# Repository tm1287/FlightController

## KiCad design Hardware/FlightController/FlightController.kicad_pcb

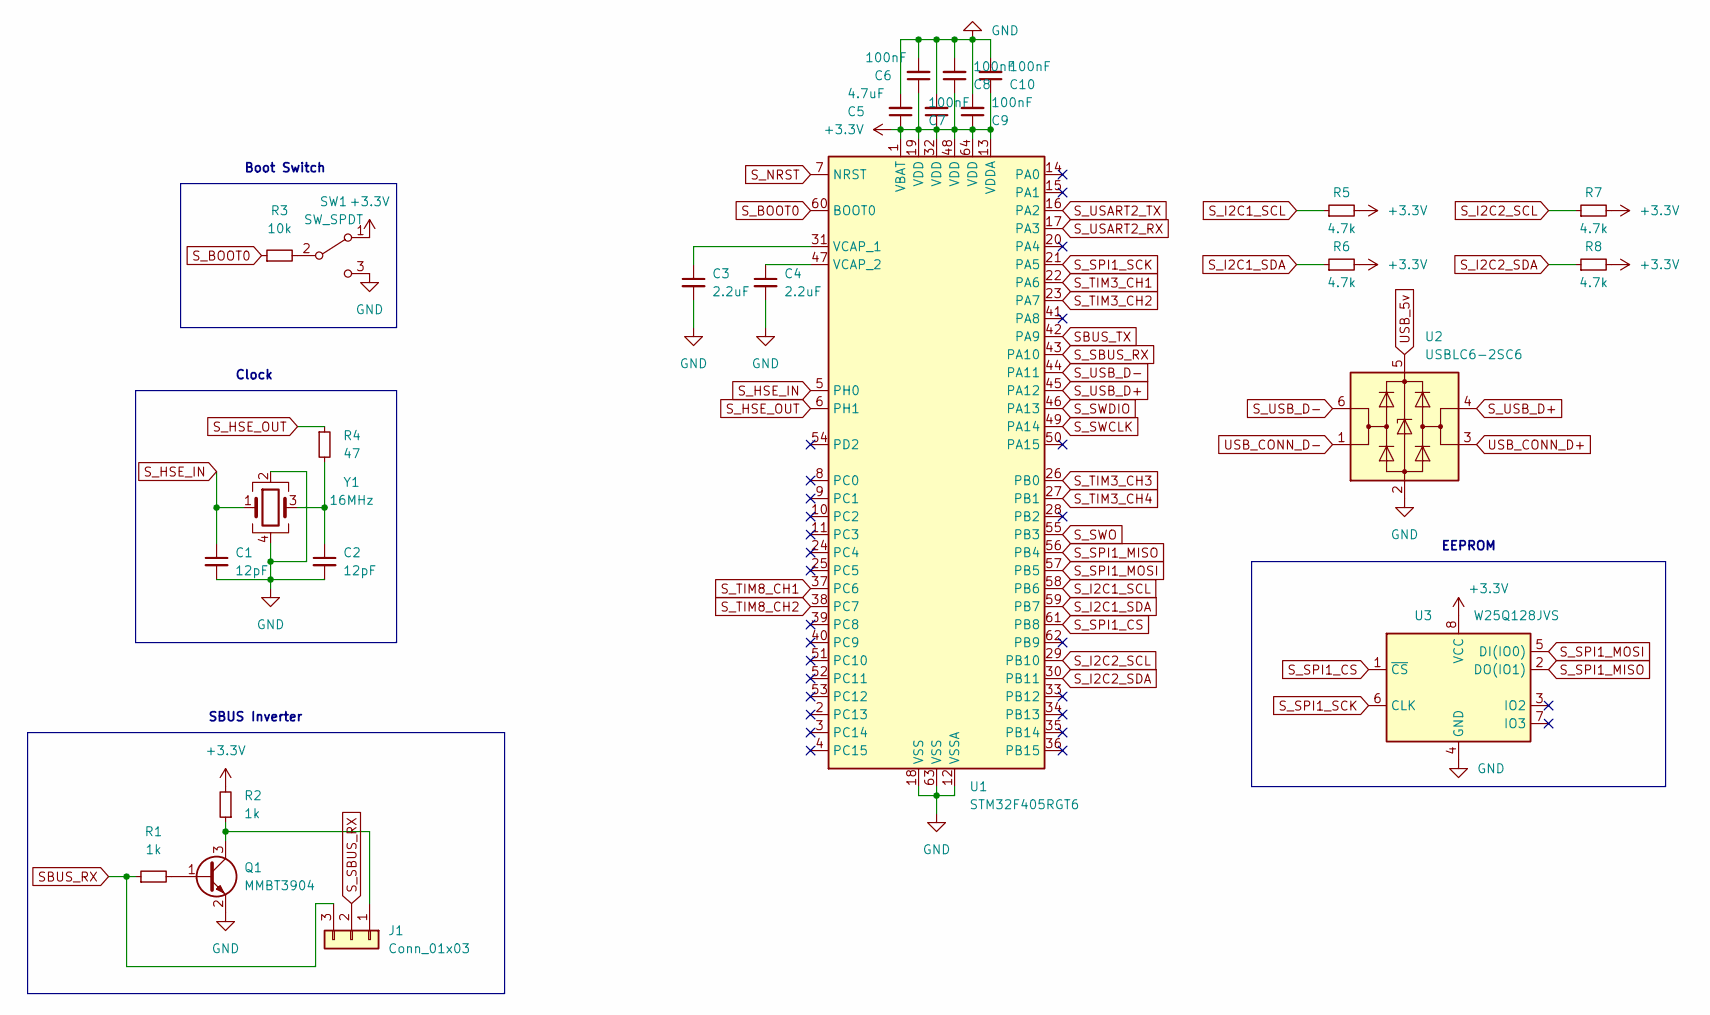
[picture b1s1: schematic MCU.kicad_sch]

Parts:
C1, C2: 12pF; C_0402_1005Metric; LCSC C1547
C3, C4: 2.2uF; C_0402_1005Metric; LCSC C12530
C5: 4.7uF; C_0603_1608Metric; LCSC C19666
C6, C7, C8, C9, C10: 100nF; C_0402_1005Metric; LCSC C1525
J1: Conn_01x03; PinHeader_1x03_P2.54mm_Vertical
Q1: MMBT3904; SOT-23; LCSC C20526
R1, R2: 1k; R_0603_1608Metric; LCSC C21190
R3: 10k; R_0603_1608Metric; LCSC C25804
R4: 47; R_0402_1005Metric; LCSC C25118
R5, R6, R7, R8: 4.7k; R_0402_1005Metric; LCSC C25900
SW1: SW_SPDT; Switch_Slide_11.6x4mm_EG1218
U1: STM32F405RGT6; LQFP-64_10x10mm_P0.5mm; LCSC C15742
U2: USBLC6-2SC6; SOT-23-6; LCSC C2827654
U3: W25Q128JVS; SOIC-8_5.23x5.23mm_P1.27mm; LCSC C97521
Y1: 16MHz; Crystal_SMD_3225-4Pin_3.2x2.5mm; LCSC C13738

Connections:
+3V3: C5.1, C6.1, C7.1, C8.1, C9.1, C10.1, R2.2, R5.2, R6.2, R7.2, R8.2, SW1.1 (A), U1.1 (VBAT), U1.13 (VDDA), U1.19 (VDD), U1.32 (VDD), U1.48 (VDD), U1.64 (VDD), U3.8 (VCC); also elsewhere on the board
GND: C1.2, C2.2, C3.2, C4.2, C5.2, C6.2, C7.2, C8.2, C9.2, C10.2, Q1.2 (E), SW1.3 (C), U1.12 (VSSA), U1.18 (VSS), U1.63 (VSS), U2.2 (GND), U3.4 (GND), Y1.2, Y1.4; also elsewhere on the board
unnamed: C2.1, R4.2, Y1.3
unnamed: C3.1, U1.31 (VCAP_1)
unnamed: C4.1, U1.47 (VCAP_2)
unnamed: J1.1, Q1.3 (C), R2.1
unnamed: Q1.1 (B), R1.2
unnamed: R3.2, SW1.2 (B)
SBUS_RX: J1.3, R1.1; also elsewhere on the board
SBUS_TX: U1.42 (PA9); also elsewhere on the board
S_BOOT0: R3.1, U1.60 (BOOT0)
S_HSE_IN: C1.1, U1.5 (PH0), Y1.1
S_HSE_OUT: R4.1, U1.6 (PH1)
S_I2C1_SCL: R5.1, U1.58 (PB6); also elsewhere on the board
S_I2C1_SDA: R6.1, U1.59 (PB7); also elsewhere on the board
S_I2C2_SCL: R7.1, U1.29 (PB10); also elsewhere on the board
S_I2C2_SDA: R8.1, U1.30 (PB11); also elsewhere on the board
S_NRST: U1.7 (NRST); also elsewhere on the board
S_SBUS_RX: J1.2, U1.43 (PA10)
S_SPI1_CS: U1.61 (PB8), U3.1 (~CS)
S_SPI1_MISO: U1.56 (PB4), U3.2 (DO(IO1))
S_SPI1_MOSI: U1.57 (PB5), U3.5 (DI(IO0))
S_SPI1_SCK: U1.21 (PA5), U3.6 (CLK)
S_SWCLK: U1.49 (PA14); also elsewhere on the board
S_SWDIO: U1.46 (PA13); also elsewhere on the board
S_SWO: U1.55 (PB3); also elsewhere on the board
S_TIM3_CH1: U1.22 (PA6); also elsewhere on the board
S_TIM3_CH2: U1.23 (PA7); also elsewhere on the board
S_TIM3_CH3: U1.26 (PB0); also elsewhere on the board
S_TIM3_CH4: U1.27 (PB1); also elsewhere on the board
S_TIM8_CH1: U1.37 (PC6); also elsewhere on the board
S_TIM8_CH2: U1.38 (PC7); also elsewhere on the board
S_USART2_RX: U1.17 (PA3); also elsewhere on the board
S_USART2_TX: U1.16 (PA2); also elsewhere on the board
S_USB_D+: U1.45 (PA12), U2.4 (I/O2)
S_USB_D-: U1.44 (PA11), U2.6 (I/O1)
USB_5v: U2.5 (VBUS); also elsewhere on the board
USB_CONN_D+: U2.3 (I/O2); also elsewhere on the board
USB_CONN_D-: U2.1 (I/O1); also elsewhere on the board

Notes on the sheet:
Clock
Boot Switch
SBUS Inverter
EEPROM

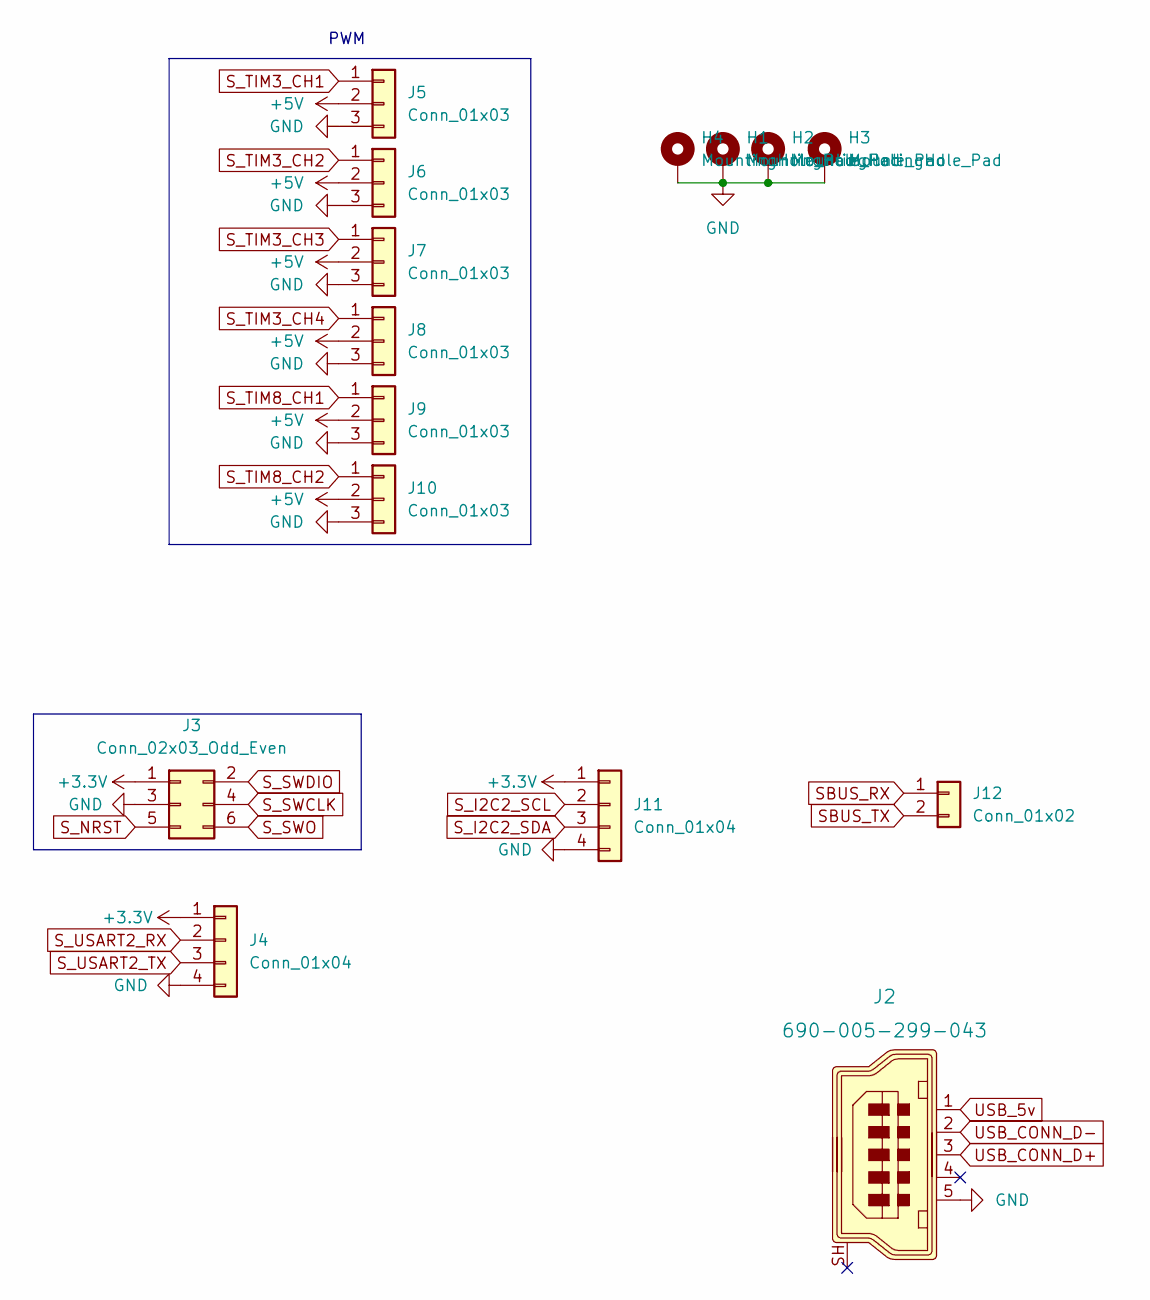
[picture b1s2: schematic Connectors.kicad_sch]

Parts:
H1, H2, H3, H4: MountingHole_Pad; MountingHole_2.5mm_Pad
J2: 690-005-299-043; USB_Mini_B_Female_690-005-299-043; MPN 690-005-299-043; Digi-Key_PN 151-1206-1-ND
J3: Conn_02x03_Odd_Even; PinHeader_2x03_P2.54mm_Vertical
J4, J11: Conn_01x04; PinHeader_1x04_P2.54mm_Vertical
J5, J6, J7, J8, J9, J10: Conn_01x03; PinHeader_1x03_P2.54mm_Vertical
J12: Conn_01x02; PinHeader_1x02_P2.54mm_Vertical

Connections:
+3V3: J3.1, J4.1, J11.1; also elsewhere on the board
+5V: J5.2, J6.2, J7.2, J8.2, J9.2, J10.2; also elsewhere on the board
GND: H1.1, H2.1, H3.1, H4.1, J2.5, J3.3, J4.4, J5.3, J6.3, J7.3, J8.3, J9.3, J10.3, J11.4; also elsewhere on the board
SBUS_RX: J12.1; also elsewhere on the board
SBUS_TX: J12.2; also elsewhere on the board
S_I2C2_SCL: J11.2; also elsewhere on the board
S_I2C2_SDA: J11.3; also elsewhere on the board
S_NRST: J3.5; also elsewhere on the board
S_SWCLK: J3.4; also elsewhere on the board
S_SWDIO: J3.2; also elsewhere on the board
S_SWO: J3.6; also elsewhere on the board
S_TIM3_CH1: J5.1; also elsewhere on the board
S_TIM3_CH2: J6.1; also elsewhere on the board
S_TIM3_CH3: J7.1; also elsewhere on the board
S_TIM3_CH4: J8.1; also elsewhere on the board
S_TIM8_CH1: J9.1; also elsewhere on the board
S_TIM8_CH2: J10.1; also elsewhere on the board
S_USART2_RX: J4.2; also elsewhere on the board
S_USART2_TX: J4.3; also elsewhere on the board

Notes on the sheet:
PWM

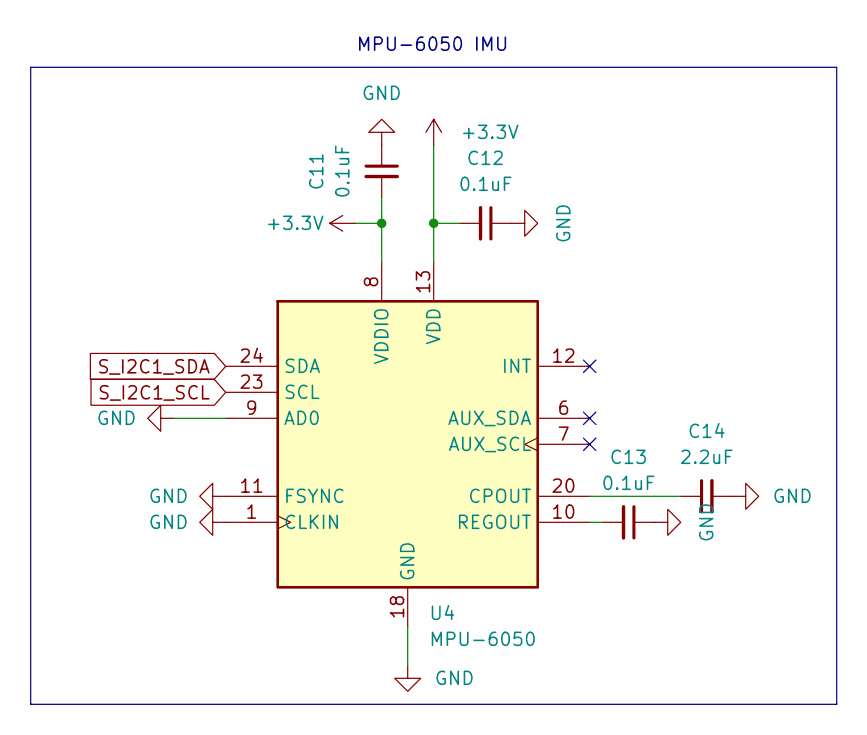
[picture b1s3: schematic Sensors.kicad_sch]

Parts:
C11, C12, C13: 0.1uF; C_0603_1608Metric_Pad1.08x0.95mm_HandSolder
C14: 2.2uF; C_0402_1005Metric; LCSC C12530
U4: MPU-6050; InvenSense_QFN-24_4x4mm_P0.5mm; LCSC C24112

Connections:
+3V3: C11.2, C12.2, U4.8 (VDDIO), U4.13 (VDD); also elsewhere on the board
GND: C11.1, C12.1, C13.1, C14.2, U4.1 (CLKIN), U4.9 (AD0), U4.11 (FSYNC), U4.18 (GND); also elsewhere on the board
unnamed: C13.2, U4.10 (REGOUT)
unnamed: C14.1, U4.20 (CPOUT)
S_I2C1_SCL: U4.23 (SCL); also elsewhere on the board
S_I2C1_SDA: U4.24 (SDA); also elsewhere on the board

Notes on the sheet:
MPU-6050 IMU

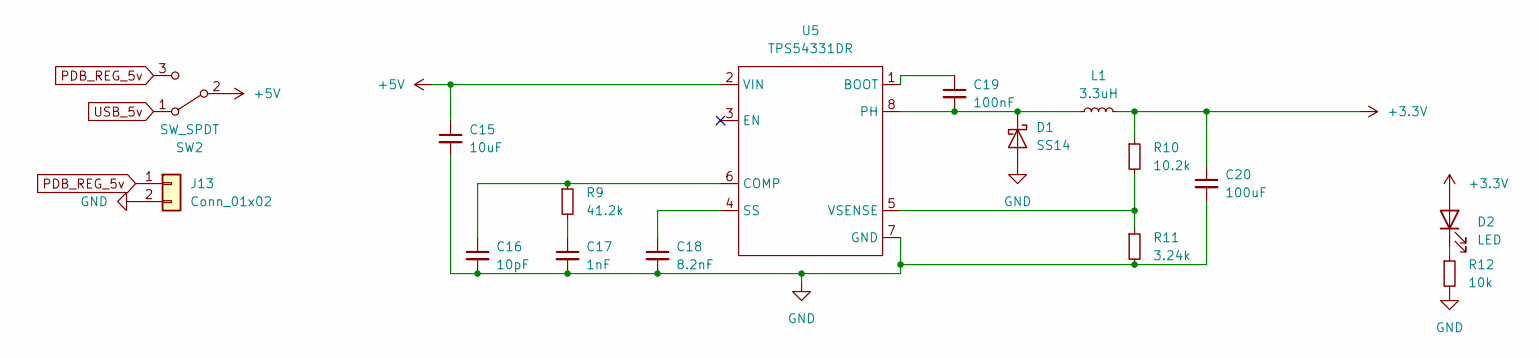
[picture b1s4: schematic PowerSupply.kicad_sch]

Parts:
C15: 10uF; C_0603_1608Metric; LCSC C96446
C16: 10pF; C_0603_1608Metric; LCSC C1634
C17: 1nF; C_0603_1608Metric; LCSC C1588
C18: 8.2nF; C_0603_1608Metric; LCSC C27920
C19: 100nF; C_0603_1608Metric; LCSC C14663
C20: 100uF; C_1206_3216Metric; LCSC C15008
D1: SS14; D_SMA; LCSC C2480
D2: LED; LED_0603_1608Metric; LCSC C2286
J13: Conn_01x02; PinHeader_1x02_P2.54mm_Vertical
L1: 3.3uH; L_1008_2520Metric_Pad1.43x2.20mm_HandSolder
R9: 41.2k; R_0603_1608Metric_Pad0.98x0.95mm_HandSolder
R10: 10.2k; R_0805_2012Metric_Pad1.20x1.40mm_HandSolder
R11: 3.24k; R_0603_1608Metric_Pad0.98x0.95mm_HandSolder
R12: 10k; R_0603_1608Metric; LCSC C25804
SW2: SW_SPDT; Switch_Slide_11.6x4mm_EG1218
U5: TPS54331DR; SOIC-8_3.9x4.9mm_P1.27mm; LCSC C9865

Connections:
+3V3: C20.1, D2.2 (A), L1.2, R10.1; also elsewhere on the board
+5V: C15.1, SW2.2 (B), U5.2 (VIN); also elsewhere on the board
GND: C15.2, C16.2, C17.2, C18.2, C20.2, D1.2 (A), J13.2, R11.2, R12.2, U5.7 (GND); also elsewhere on the board
unnamed: C16.1, R9.1, U5.6 (COMP)
unnamed: C17.1, R9.2
unnamed: C18.1, U5.4 (SS)
unnamed: C19.1, U5.1 (BOOT)
unnamed: C19.2, D1.1 (K), L1.1, U5.8 (PH)
unnamed: D2.1 (K), R12.1
unnamed: R10.2, R11.1, U5.5 (VSENSE)
PDB_REG_5v: J13.1, SW2.3 (C)
USB_5v: SW2.1 (A); also elsewhere on the board

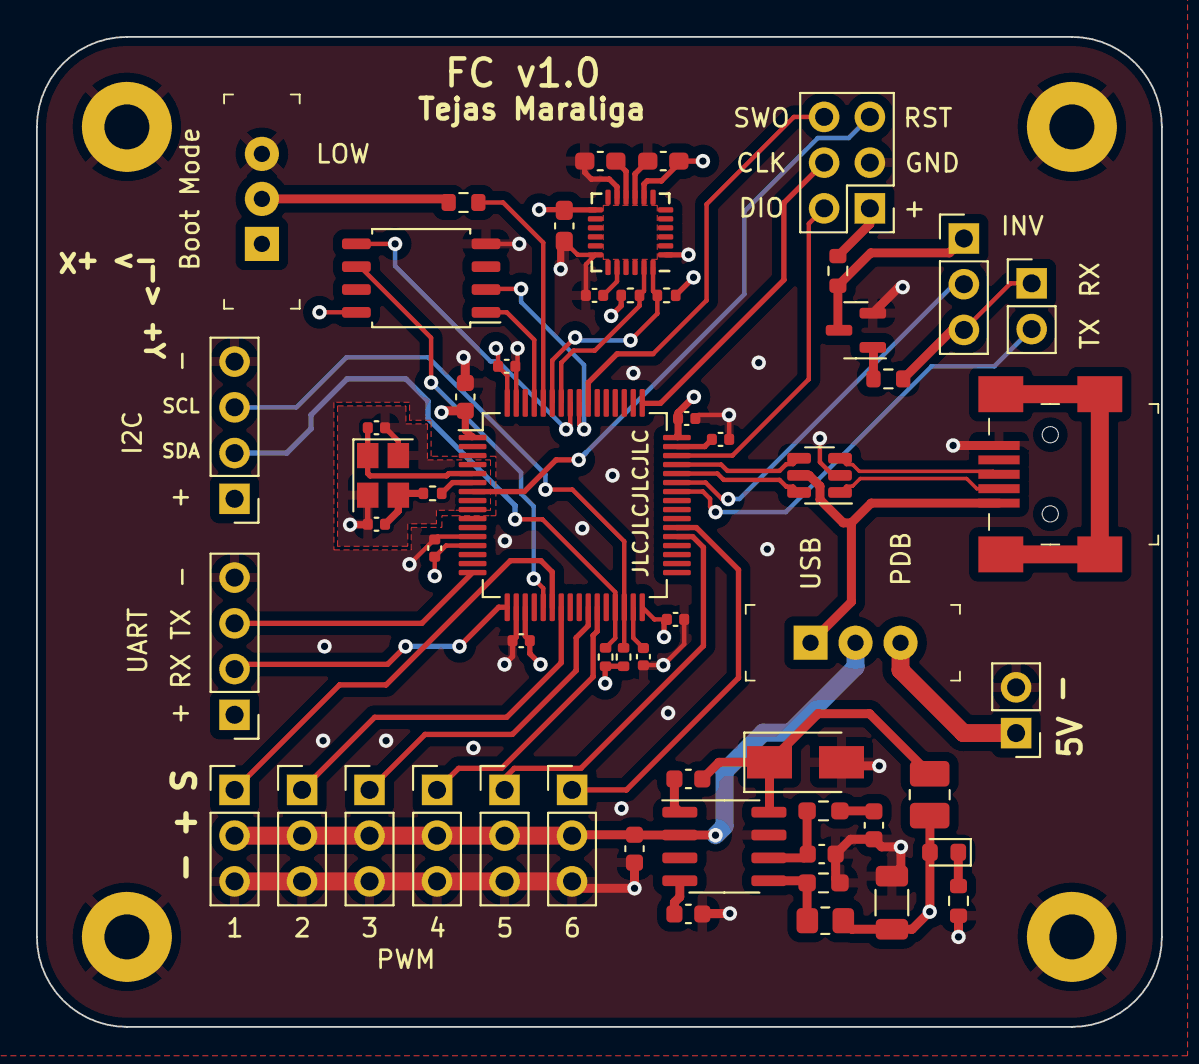
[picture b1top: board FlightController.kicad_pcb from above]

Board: 4 copper layers, 62.5 x 55.0 mm, 61 parts (0 on the bottom side), 50 nets.

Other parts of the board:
Je: 690-005-299-043; USB_Mini_B_Female_690-005-299-043

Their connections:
GND: Je.5; also elsewhere on the board
USB_5v: Je.1; also elsewhere on the board
USB_CONN_D+: Je.3; also elsewhere on the board
USB_CONN_D-: Je.2; also elsewhere on the board

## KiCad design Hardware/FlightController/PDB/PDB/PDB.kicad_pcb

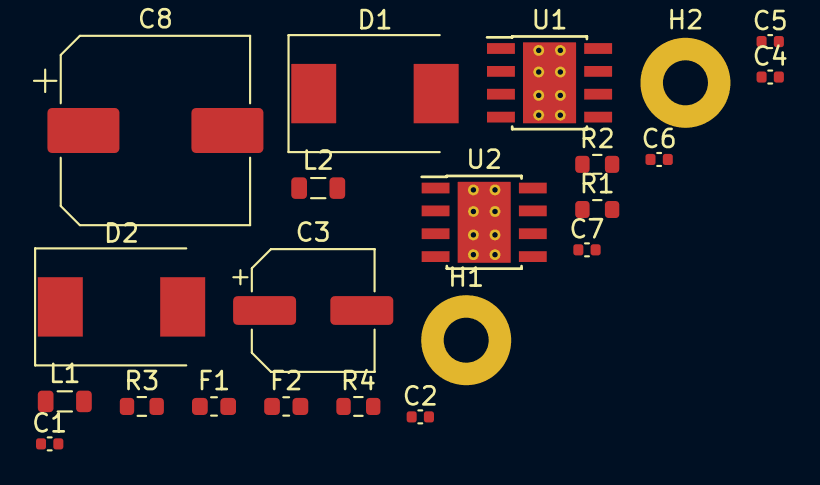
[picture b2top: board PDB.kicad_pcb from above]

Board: 2 copper layers, 22 parts (0 on the bottom side), 10 nets, no tracks yet.

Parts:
C1, C2, C4, C5, C6, C7: 10uF; C_0402_1005Metric
C3: 330uF; CP_Elec_6.3x5.8
C8: 220uF; CP_Elec_10x10
D1, D2: B340; D_SMC
F1, F2: 750mA; Fuse_0603_1608Metric
H1, H2: MountingHole_Pad; MountingHole_2.5mm_Pad
L1, L2: 22 uH; L_0805_2012Metric
R1, R3: 10k; R_0603_1608Metric
R2: 5.9k; R_0603_1608Metric
R4: 3.24k; R_0603_1608Metric
U1, U2: TPS5430DDA; TI_SO-PowerPAD-8_ThermalVias

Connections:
+BATT: C1.1, C4.1, C5.1, C6.1, H1.1, U1.7 (VIN), U2.7 (VIN)
GND: C1.2, C3.2, C4.2, C5.2, C6.2, C8.2, D1.2 (A), D2.2 (A), H2.1, R2.2, R4.2, U1.6 (GND), U1.9 (GNDPAD), U2.6 (GND), U2.9 (GNDPAD)
unnamed: C2.1, U1.1 (BOOT)
unnamed: C2.2, D1.1 (K), L1.1, U1.8 (PH)
unnamed: C3.1, F1.1, L1.2, R1.1
unnamed: C7.1, U2.1 (BOOT)
unnamed: C7.2, D2.1 (K), L2.1, U2.8 (PH)
unnamed: C8.1, F2.1, L2.2, R3.1
unnamed: R1.2, R2.1, U1.4 (VSENSE)
unnamed: R3.2, R4.1, U2.4 (VSENSE)

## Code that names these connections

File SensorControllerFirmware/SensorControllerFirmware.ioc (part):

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Mcu.Name=STM32F405RGTx
Mcu.Package=LQFP64
Mcu.UserName=STM32F405RGTx
PA10.Mode=Asynchronous
PA10.Signal=USART1_RX
PA11.Mode=Device_Only
PA11.Signal=USB_OTG_FS_DM
PA12.Mode=Device_Only
PA12.Signal=USB_OTG_FS_DP
PA13.Mode=Trace_Asynchronous_SW
PA13.Signal=SYS_JTMS-SWDIO
PA14.Mode=Trace_Asynchronous_SW
PA14.Signal=SYS_JTCK-SWCLK
PA2.Mode=Asynchronous
PA2.Signal=USART2_TX
PA3.Mode=Asynchronous
PA3.Signal=USART2_RX
PA5.Mode=Full_Duplex_Master
PA5.Signal=SPI1_SCK
PA6.Signal=S_TIM3_CH1
PA7.Signal=S_TIM3_CH2
PA9.Mode=Asynchronous
PA9.Signal=USART1_TX
PB0.Signal=S_TIM3_CH3
PB1.Signal=S_TIM3_CH4
PB10.Mode=I2C
PB10.Signal=I2C2_SCL
PB11.Mode=I2C
PB11.Signal=I2C2_SDA
PB3.Mode=Trace_Asynchronous_SW
PB3.Signal=SYS_JTDO-SWO
PB4.Mode=Full_Duplex_Master
PB4.Signal=SPI1_MISO
PB5.Mode=Full_Duplex_Master
PB5.Signal=SPI1_MOSI
PB6.Mode=I2C
PB6.Signal=I2C1_SCL
PB7.Mode=I2C
PB7.Signal=I2C1_SDA
PB8.GPIOParameters=PinState,GPIO_Label
PB8.GPIO_Label=EEPROM_CS
PB8.PinState=GPIO_PIN_SET
PB8.Signal=GPIO_Output
PC6.Signal=S_TIM8_CH1
PC7.Signal=S_TIM8_CH2
PH0-OSC_IN.Mode=HSE-External-Oscillator
PH0-OSC_IN.Signal=RCC_OSC_IN
PH1-OSC_OUT.Mode=HSE-External-Oscillator
PH1-OSC_OUT.Signal=RCC_OSC_OUT
RCC.HSE_VALUE=16000000
RCC.SYSCLKFreq_VALUE=168000000
RCC.SYSCLKSource=RCC_SYSCLKSOURCE_PLLCLK
board=custom

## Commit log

2022-05-31 Add Sensor MCU schematic items
2022-05-31 Rename firmware for transparency
2022-05-31 Add ICM-42670-P symbol and schematic
2022-06-09 Round out basic schematic and add preliminary board layout
2022-06-13 Add and route SBUS inverter
2022-06-15 Update footprints to be digikey compliant
2022-06-16 Update footprints, routing and LCSC numbers
2022-06-21 Finalize design and routing for v1.0 fab
2022-06-21 Generate code for STM32CubeIDE
2022-07-06 Add simple I2C and USB testing code
2022-07-06 Read and stream acceleration values from MPU6050
2022-07-06 Calculate basic pitch and roll through acceleration values.
2022-07-06 Add base files for python AttitudeVisualizer
2022-07-07 Move IMU initialization and polling into functions
2022-07-07 Populate visualizer with 3-axis projection
2022-07-07 Add complementary filter for estimating pitch and roll
2022-07-07 Abstract MPU6050 functions into driver interface
2022-07-07 Update clock speed and timer prescalers
2022-07-11 Incomplete EEPROM driver
2022-07-13 Start porting I2Cdev MPU6050 DMP functions to C
2022-07-13 Remove extraneous files
